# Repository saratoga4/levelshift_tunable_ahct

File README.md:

# Universal level shifter

This project contains KiCAD files for a 3-3V->5V level shifter that can drive aribtrary impedance lines using a potentiometer to continously adjust impedance. Labels are provided for typical wire types, including 3-wire cable, 75 ohm coax, 100 ohm twisted pair, and higher impedance 2-wire cables.  

# BOM

A bill of materials with Digikey part numbers is provided:  [bom/ibom.html](https://htmlpreview.github.io/?https://github.com/saratoga4/levelshift_tunable_ahct/blob/main/bom/ibom.html)

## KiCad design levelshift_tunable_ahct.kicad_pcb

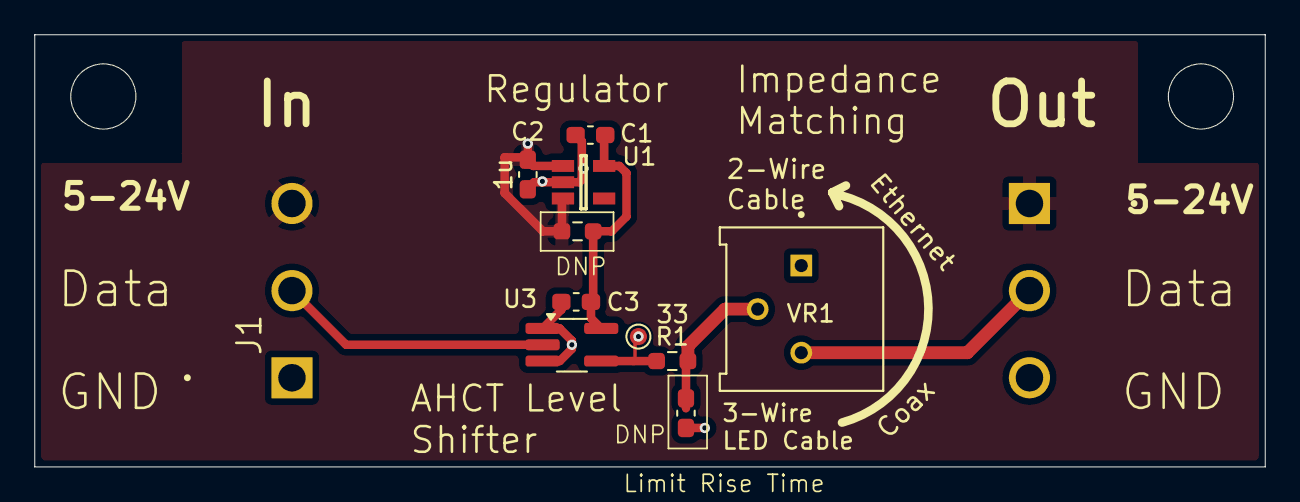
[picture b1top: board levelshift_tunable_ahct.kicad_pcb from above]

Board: 2 copper layers, 71.8 x 25.2 mm, 12 parts (0 on the bottom side), 7 nets.

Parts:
C1, C2, C3: 1u; C_0603_1608Metric_Pad1.08x0.95mm_HandSolder
C4: 500pF; C_0603_1608Metric_Pad1.08x0.95mm_HandSolder
J1, J2: Screw_Terminal_01x03; CUI_TB004-508-03BE
R1: 33; R_0603_1608Metric_Pad0.98x0.95mm_HandSolder
R3: R_0603_1608Metric_Pad0.98x0.95mm_HandSolder
TP1: TestPoint; TestPoint_Pad_D1.0mm
U1: NCP730ASN500T1G; DBV0005A_M
U3: 74AHCT1G125; TSOT-23-5_HandSoldering
VR1: 3386P-1-101TLF; TRIM_3386P-1-101TLF

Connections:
+5V: C1.1, C3.1, R3.2, U1.5 (OUT), U3.5 (VCC)
/Vin: C2.1, J1.3, J2.1, R3.1, U1.1 (IN), U1.3 (EN)
/signal_in: J1.2, U3.2
GND: C1.2, C2.2, C3.2, C4.2, J1.1, J2.3, U1.2 (GND), U3.1, U3.3 (GND)
unnamed: C4.1, R1.2, VR1.2
unnamed: J2.2, VR1.3
unnamed: R1.1, U3.4

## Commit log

2026-04-01 Check in universal level shifter kicad files
2026-04-01 Add git ignore file for kicad
2026-04-01 Check in project
2026-04-01 Force LF line endings via .gitattributes
2026-04-01 Add board image
2026-04-01 Update to KiCAD 10
2026-04-01 Update BOM with digikey part numbers
2026-04-01 Don't include project backups
